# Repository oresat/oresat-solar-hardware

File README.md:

# OreSat Solar Modules

This repo contains the CAD for [OreSat's](oresat.org) solar modules. Part of OreSat's design is a module bus system that spans 1 - 3 U, so each array is its own 1U "panel". Oresat0, a 1U CubeSat, thus has 4 solar modules, and OreSat1, a 2U CubeSat, has 8. This approach has pretty severe drawbacks in terms of solar cell coverage area, but it's extremely flexible for having one design across a bunch of different designs. One nifty part of this design is that each 1u panel has its own **true** maximum power point tracker, with a software-defined MPPT algorithm. We're MPPT elitists - we eschew maximum power point "controllers" and think if it's not doing true power point optimization, you're just doing it wrong.

That and coffee. You're all doing coffee wrong, too, but we don't hold that against you, you don't live in Portland, we understand.

We've flown our GaAs solar cell design, and are currently workingon our silicon design.

# Design Notes

**Status, design, construction, and testing information can be found in the [OreSat Solar Module Design Notes](https://docs.google.com/document/d/1mogZjYhJievwLsnVkg4Q0sEF9xPMA5q7KPciky3YWKE/edit?usp=sharing).**

# Pretty Pictures

## LICENSE

Copyright the Portland State Aerospace Society, 2025.

This source describes Open Hardware that is licensed under CERN-OHL-S v2, or any later version.

You may redistribute and modify this source and make products using it under the terms of the CERN-OHL-S v2 (https://ohwr.org/cern_ohl_s_v2.txt).

This source is distributed WITHOUT ANY EXPRESS OR IMPLIED WARRANTY, INCLUDING OF MERCHANTABILITY, SATISFACTORY QUALITY AND FITNESS FOR A PARTICULAR PURPOSE. Please see the CERN-OHL-S v2 for applicable conditions.

Source location: https://github.com/oresat/

If you require a different license for this open hardware project, please contact us at [oresat@pdx.edu](mailto:oresat@pdx.edu).

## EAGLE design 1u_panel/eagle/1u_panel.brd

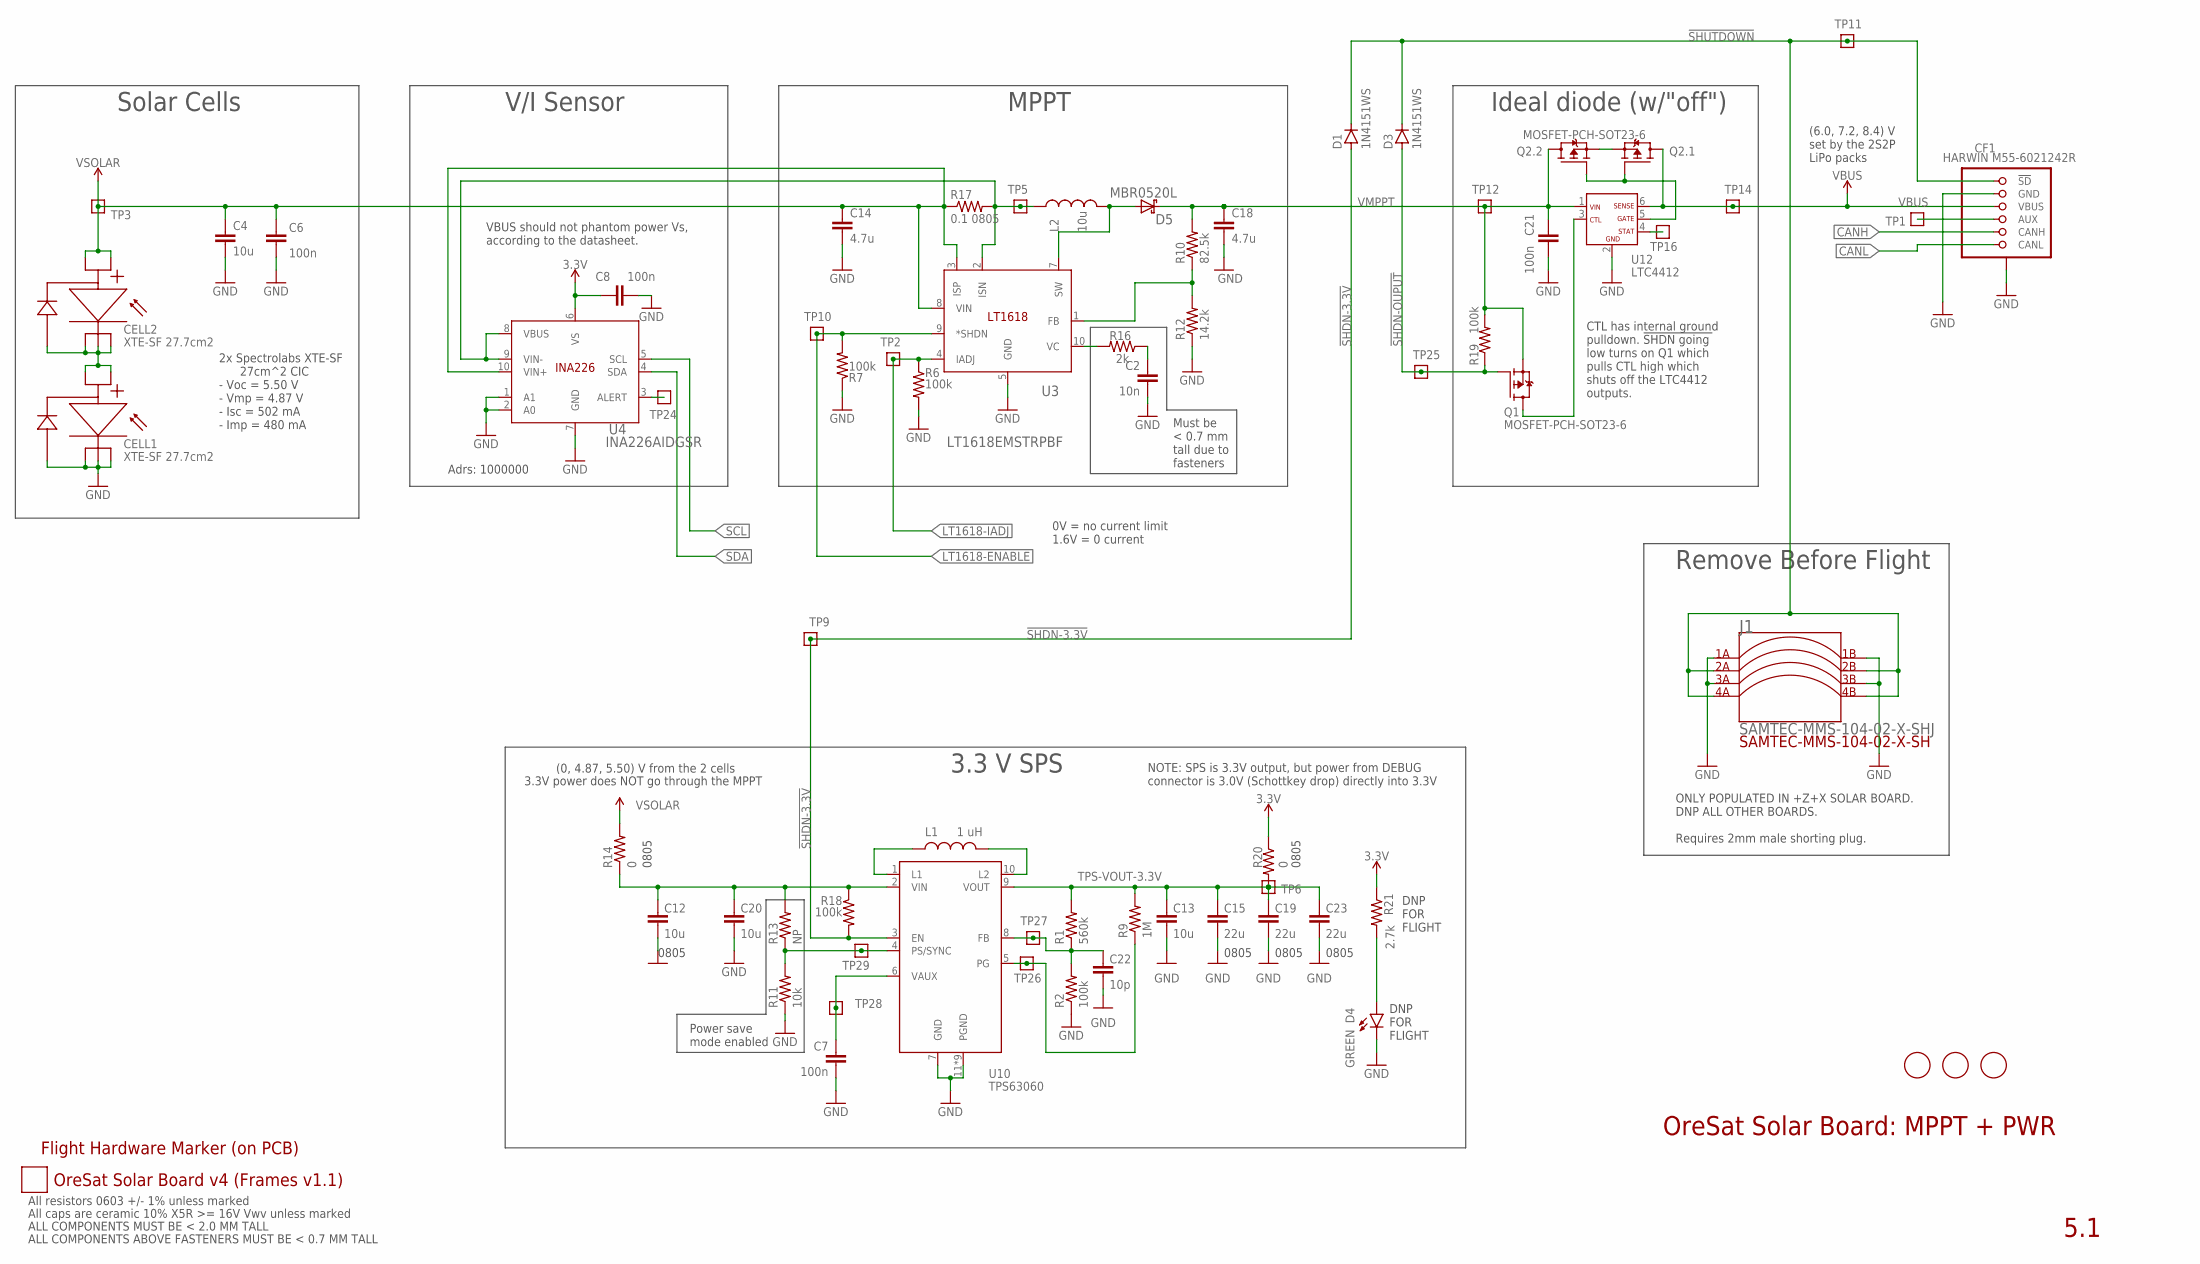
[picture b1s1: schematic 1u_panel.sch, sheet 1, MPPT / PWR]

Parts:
C2: 10n; .0603-C-NOSILK; MPN UMK107B7103KAHT
C4, C13, C20: 10u; .0603-C-NOSILK; MPN GRT188R61C106KE13D
C6, C7, C8: 100n; .0603-C-NOSILK; MPN CL10B104KB85PND
C12: 10u; .0805-B-NOSILK; MPN GRT21BR61C106KE01L
C14, C18: 4.7u; .0603-C-NOSILK; MPN EMK107BBJ475KAHT
C15, C19, C23: 22u; .0805-B-NOSILK; MPN CL32B226KOJVPNE
C21: 100n; .0402-B-NOSILK; MPN CL10B104KB85PND
C22: 10p; .0603-C-NOSILK; MPN GRT188R61C106KE13D
CELL1, CELL2: XTE-SF 27.7cm2; SPECTROLAB-XTE-SF
CF1: HARWIN M55-6021242R; HARWIN-M55-60X1242R
D1, D3: 1N4151WS; SOD323-R
D4: GREEN; LED-0603; MPN IN-S63AT5A
D5: MBR0520L; SOD123; MPN NRVB130T3G
J1: SAMTEC-MMS-104-02-X-SHJ; SAMTEC-MMS-104-02-X-SH
L1: 1 uH; IND_1226AS-H-1R0N=P2; MPN VLS3010CX-1R5M-1
L2: 10u; NONSTANDARD; MPN 744042100
PCB1: ORESAT-SOLAR-BOARD-V4-SPECTROLABS; ORESAT-SOLAR-BOARD-V4
Q1: MOSFET-PCH-SOT23-6; SOT23-6; MPN DMP3050LVT-7
Q2: MOSFET-PCH-SOT23-6; SOT23-6; MPN DMP2240UDM-7
R1: 560k; .0603-C-NOSILK; MPN CRGCQ0603F470K
R2: 100k; .0603-C-NOSILK; MPN RR0816P-104-D
R6, R7, R18, R19: 100k; .0603-C-NOSILK; MPN RNCP0603FTD10K0
R9: 1M; .0603-C-NOSILK
R10: 82.5k; .0603-C-NOSILK; MPN ERA-3AEB8252V
R11: 10k; .0603-C-NOSILK
R12: 14.2k; .0603-C-NOSILK; MPN RN73R1JTTD1422D25
R13: NP; .0603-C-NOSILK; MPN RNCP0603FTD10K0
R14, R20: 0; .0805-C-NOSILK; MPN RMCF0805ZT0R00
R16: 2k; .0603-C-NOSILK; MPN RK73H1JTTD2001F
R17: 0.1 0805; .0805-C-NOSILK; MPN RMCF0805ZT0R00
R21: 2.7k; .0603-C-NOSILK; MPN CRGCQ0603F2K7
TP1, TP2, TP3, TP5, TP6, TP9, TP10, TP11, TP12, TP14, TP16, TP24, TP25, TP26, TP27, TP28, TP29: TEST-POINT-LARGE-SQUARE; 1X01
U3: LT1618EMSTRPBF; MSOP-10_MS; MPN LT1618EMS#TRPBF
U4: INA226AIDGSR; DGS10; MPN INA226AIDGSR
U10: TPS63060; CONV_TPS63060DSCT
U12: LTC4412; SOT23-6; MPN LTC4412ES6#TRPBF
U$1: FLIGHMARKERNEW; FLIGHTMARKER_NEW_BOARDS
U$2, U$3, U$4: FIDUCIAL; FIDUCIAL_1MM

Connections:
3.3V: C8.1, R20.1, R21.1, U4.6 (VS); also elsewhere on the board
4412-CTL: Q1.1 (D), Q1.2 (D), Q1.5 (D), Q1.6 (D), U12.3 (CTL)
4412-GATE: Q2.1 (G), Q2.3 (G), U12.5 (GATE)
!SHDN-3.3V: D1.A, R18.2, TP9.1, U10.3 (EN)
!SHDN-OUPUT: D3.A, Q1.3 (G), R19.1, TP25.1
!SHUTDOWN: CF1.1 (!SD), CF1.2 (!SD), D1.C, D3.C, J1.2A, J1.2B, J1.4A, J1.4B, TP11.1
AUX: CF1.7 (AUX), CF1.8 (AUX), TP1.1
CANH: CF1.9 (CANH), CF1.10 (CANH); also elsewhere on the board
CANL: CF1.11 (CANL), CF1.12 (CANL); also elsewhere on the board
GND: C2.2, C4.2, C6.2, C7.2, C8.2, C12.2, C13.2, C14.2, C15.2, C18.2, C19.2, C20.2, C21.2, C22.2, C23.2, CELL1.NEG1 (C1), CELL1.NEG2 (C2), CELL1.NEG3 (C3), CELL1.NEG4 (C4), CF1.3 (GND), CF1.4 (GND), CF1.P$1 (SHIELD), CF1.P$2 (SHIELD), CF1.P$3 (SHIELD), CF1.P$4 (SHIELD), D4.C, J1.1A, J1.1B, J1.3A, J1.3B, R2.1, R6.2, R7.1, R11.1, R12.1, U3.5 (GND), U4.1 (A1), U4.2 (A0), U4.7 (GND), U10.7 (GND), U10.11 (PGND), U10.12 (PGND), U10.13 (PGND), U10.14 (PGND), U10.15 (PGND), U10.16 (PGND), U10.17 (PGND), U10.18 (PGND), U10.19 (PGND), U12.2 (GND); also elsewhere on the board
INTERCELL: CELL1.POS1 (A1), CELL1.POS2 (A2), CELL2.NEG1 (C1), CELL2.NEG2 (C2), CELL2.NEG3 (C3), CELL2.NEG4 (C4)
LT1618-ENABLE: R7.2, TP10.1, U3.9 (*SHDN); also elsewhere on the board
LT1618-FB: R10.1, R12.2, U3.1 (FB)
LT1618-IADJ: R6.1, TP2.1, U3.4 (IADJ); also elsewhere on the board
LT1618-ISN: L2.P$1 (1), R17.2, TP5.1, U3.2 (ISN), U4.8 (VBUS), U4.9 (VIN-)
LT1618-SW: D5.A (ANODE), L2.P$2 (2), U3.7 (SW)
LT1618-VC: R16.2, U3.10 (VC)
unnamed: TP24.1, U4.3 (ALERT)
unnamed: C2.1, R16.1
unnamed: TP16.1, U12.4 (STAT)
unnamed: Q2.2 (S), Q2.5 (S)
unnamed: D4.A, R21.2
SCL: U4.5 (SCL); also elsewhere on the board
SDA: U4.4 (SDA); also elsewhere on the board
TPS-EN: R11.2, R13.1, TP29.1, U10.4 (PS/SYNC)
TPS-FB: C22.1, R1.1, R2.2, TP27.1, U10.8 (FB)
TPS-L1: L1.1, U10.1 (L1)
TPS-L2: L1.2, U10.10 (L2)
TPS-PG: R9.1, TP26.1, U10.5 (PG)
TPS-VAUX: C7.1, TP28.1, U10.6 (VAUX)
TPS-VIN: C12.1, C20.1, R13.2, R14.1, R18.1, U10.2 (VIN)
TPS-VOUT-3.3V: C13.1, C15.1, C19.1, C23.1, R1.2, R9.2, R20.2, TP6.1, U10.9 (VOUT)
VBUS: CF1.5 (VBUS), CF1.6 (VBUS), Q2.6 (D), TP14.1, U12.6 (SENSE)
VMPPT: C18.1, C21.1, D5.K (CATHODE), Q1.4 (S), Q2.4 (D), R10.2, R19.2, TP12.1, U12.1 (VIN)
VSOLAR: C4.1, C6.1, C14.1, CELL2.POS1 (A1), CELL2.POS2 (A2), R14.2, R17.1, TP3.1, U3.3 (ISP), U3.8 (VIN), U4.10 (VIN+)

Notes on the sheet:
2x Spectrolabs XTE-SF 27cm^2 CIC - Voc = 5.50 V - Vmp = 4.87 V - Isc = 502 mA - Imp = 480 mA
OreSat Solar Board: MPPT + PWR
5.1
V/I Sensor
MPPT
All resistors 0603 +/- 1% unless marked
All caps are ceramic 10% X5R >= 16V Vwv unless marked
0805
(0, 4.87, 5.50) V from the 2 cells
(6.0, 7.2, 8.4) V set by the 2S2P LiPo packs
3.3 V SPS
VBUS should not phantom power Vs, according to the datasheet.
Adrs: 1000000
CTL has internal ground pulldown. !SHDN going low turns on Q1 which pulls CTL high which shuts off the LTC4412 outputs.
ALL COMPONENTS MUST BE < 2.0 MM TALL
ALL COMPONENTS ABOVE FASTENERS MUST BE < 0.7 MM TALL
3.3V power does NOT go through the MPPT
Must be < 0.7 mm tall due to fasteners
0V = no current limit 1.6V = 0 current
NOTE: SPS is 3.3V output, but power from DEBUG connector is 3.0V (Schottkey drop) directly into 3.3V
Solar Cells
Ideal diode (w/"off")
Remove Before Flight
ONLY POPULATED IN +Z+X SOLAR BOARD. DNP ALL OTHER BOARDS. Requires 2mm male shorting plug.
DNP FOR FLIGHT
Power save mode enabled

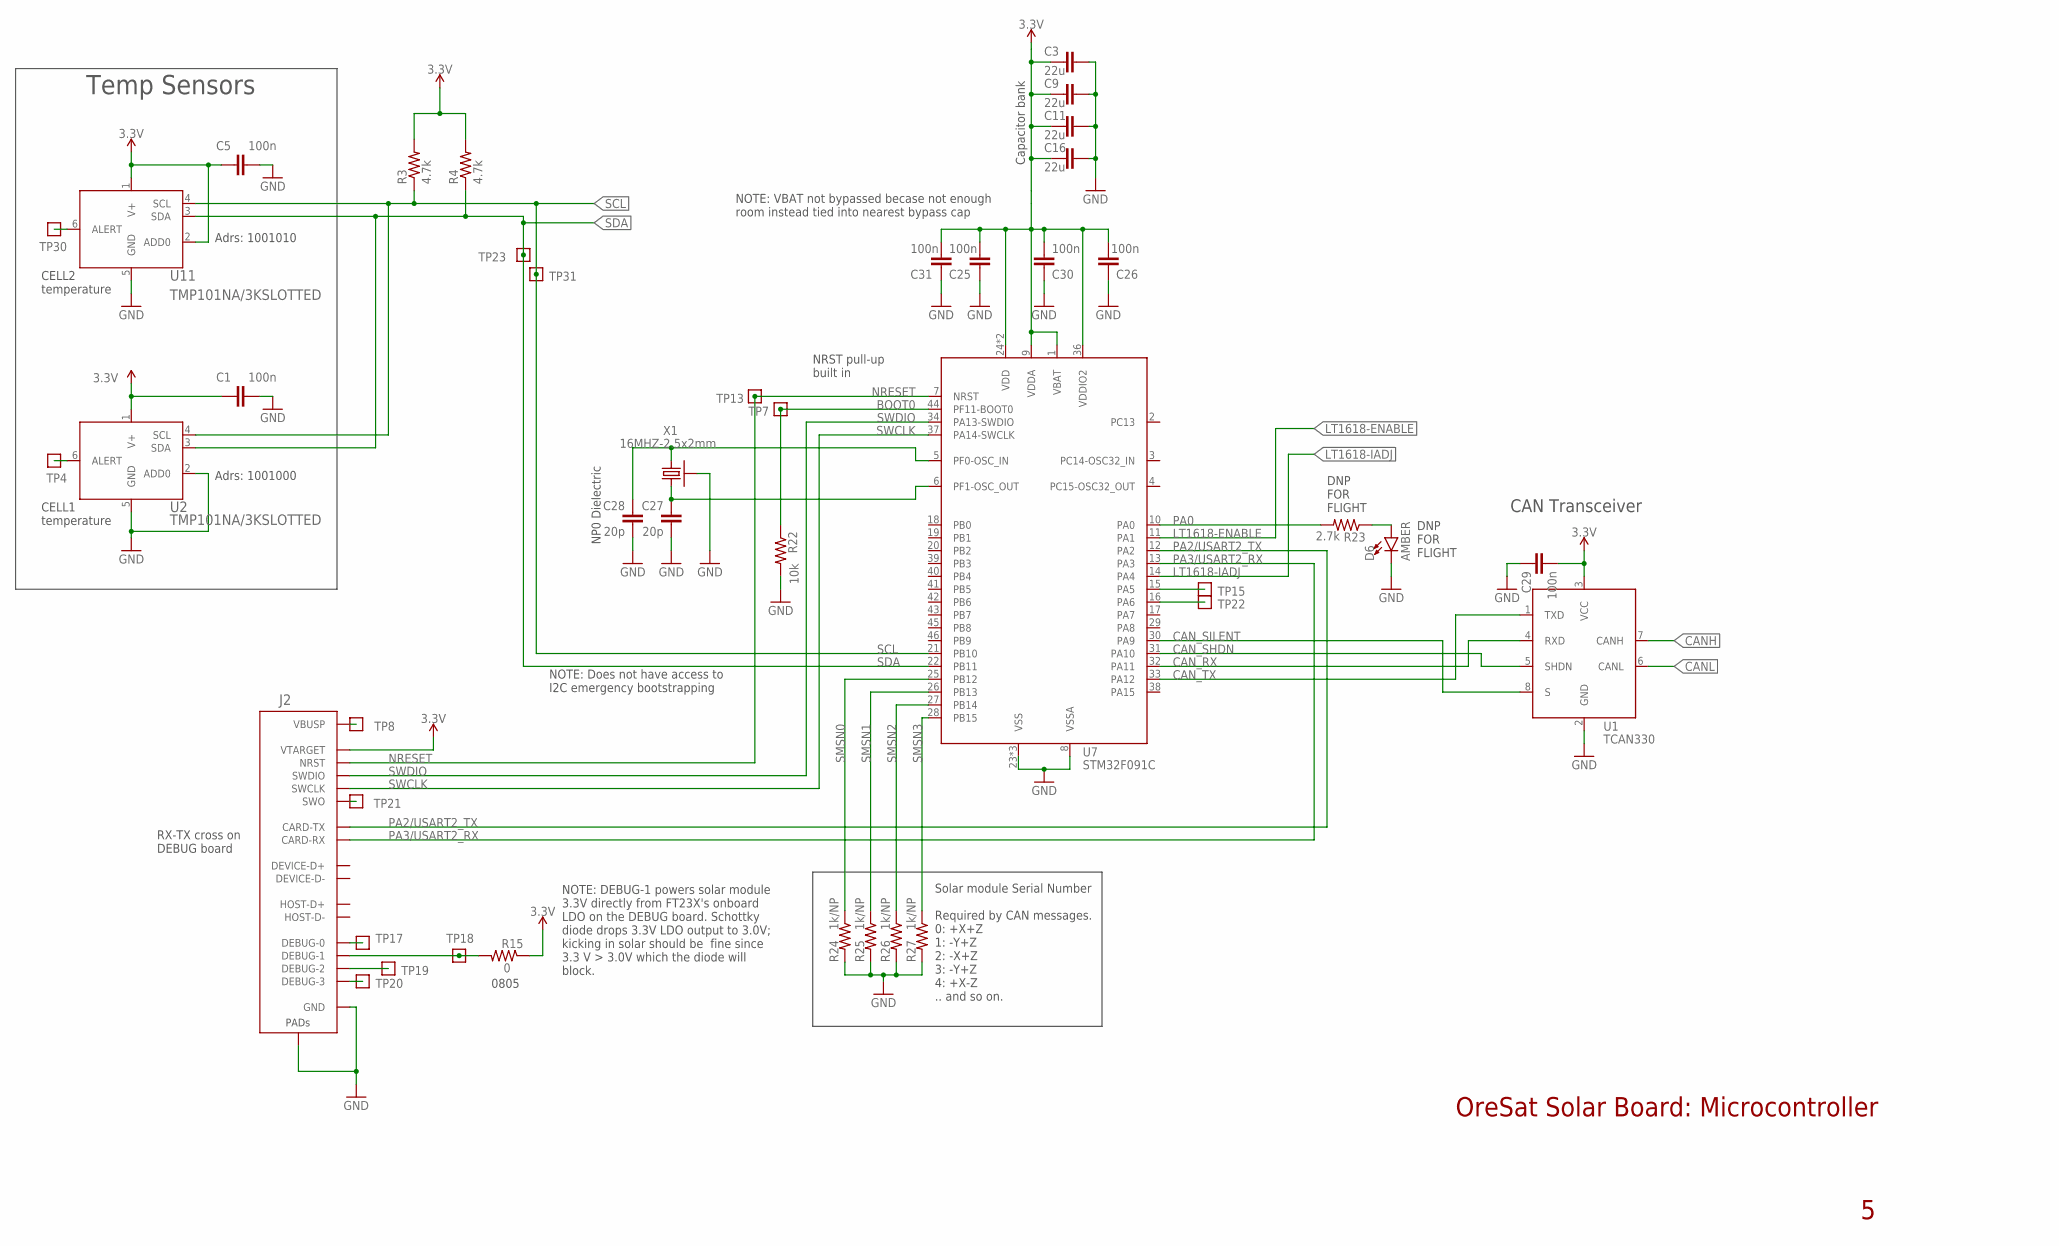
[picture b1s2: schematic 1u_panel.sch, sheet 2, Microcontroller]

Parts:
C1, C5, C25, C26, C29, C30, C31: 100n; .0603-C-NOSILK; MPN CL10B104KB85PND
C3, C9, C11, C16: 22u; .0805-B-NOSILK; MPN CL32B226KOJVPNE
C27, C28: 20p; .0603-C-NOSILK; MPN GCM1885C2A200JA16D
D6: AMBER; LED-0603; MPN IN-S63AT5A
J2: ORESAT-DEBUG-CONNECTOR-ALL; TE_2-1734592-0; MPN 687120183622
R3, R4: 4.7k; .0603-C-NOSILK; MPN RE0603FRE074K7L
R15: 0; .0805-C-NOSILK; MPN RMCF0805ZT0R00
R22: 10k; .0603-C-NOSILK; MPN CRGCQ0603F2K7
R23: 2.7k; .0603-C-NOSILK; MPN CRGCQ0603F2K7
R24, R25, R26, R27: 1k/NP; .0603-C-NOSILK; MPN CR0603AFX-1001ELF
TP4, TP7, TP8, TP13, TP15, TP17, TP18, TP19, TP20, TP21, TP22, TP23, TP30, TP31: TEST-POINT-LARGE-SQUARE; 1X01
U1: TCAN330; SOT23-8_TI-DCN; MPN TCAN330GDCNT
U2, U11: TMP101NA/3KSLOTTED; DBV6-SLOT; MPN TMP101NA/3K
U7: STM32F091C; MPN STM32F091CCT6TR
X1: 16MHZ-2.5x2mm; CRYSTAL_2.5X2; MPN ECS-160-10-36Q-ES-TR

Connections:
3.3V: C1.1, C3.1, C5.1, C9.1, C11.1, C16.1, C25.2, C26.2, C29.2, C30.2, C31.2, J2.11 (VTARGET), R3.2, R4.2, R15.1, U1.3 (VCC), U2.1 (V+), U7.1 (VBAT), U7.9 (VDDA), U7.24 (VDD), U7.36 (VDDIO2), U7.48 (VDD), U11.1 (V+), U11.2 (ADD0); also elsewhere on the board
BOOT0: R22.1, TP7.1, U7.44 (PF11-BOOT0)
CANH: U1.7 (CANH); also elsewhere on the board
CANL: U1.6 (CANL); also elsewhere on the board
CAN_RX: U1.4 (RXD), U7.32 (PA11)
CAN_SHDN: U1.5 (SHDN), U7.31 (PA10)
CAN_SILENT: U1.8 (S), U7.30 (PA9)
CAN_TX: U1.1 (TXD), U7.33 (PA12)
DEBU-1/SOLAR3V: J2.18 (DEBUG-1), R15.2, TP18.1
DEBUG-0: J2.17 (DEBUG-0), TP17.1
DEBUG-2: J2.19 (DEBUG-2), TP19.1
DEBUG-3: J2.20 (DEBUG-3), TP20.1
GND: C1.2, C3.2, C5.2, C9.2, C11.2, C16.2, C25.1, C26.1, C27.2, C28.2, C29.1, C30.1, C31.1, D6.C, J2.3 (GND), J2.6 (GND), J2.9 (GND), J2.PAD1 (PAD), J2.PAD2 (PAD), R22.2, R24.2, R25.2, R26.2, R27.2, U1.2 (GND), U2.2 (ADD0), U2.5 (GND), U7.8 (VSSA), U7.23 (VSS), U7.35 (VSS), U7.47 (VSS), U11.5 (GND), X1.2 (SHIELD), X1.4 (SHIELD); also elsewhere on the board
LT1618-ENABLE: U7.11 (PA1); also elsewhere on the board
LT1618-IADJ: U7.14 (PA4); also elsewhere on the board
unnamed: J2.1 (VBUSP), J2.2 (VBUSP), TP8.1
unnamed: TP4.1, U2.6 (ALERT)
unnamed: TP30.1, U11.6 (ALERT)
unnamed: D6.A, R23.1
NRESET: J2.10 (NRST), TP13.1, U7.7 (NRST)
PA0: R23.2, U7.10 (PA0)
PA2/USART2_TX: J2.13 (CARD-TX), U7.12 (PA2)
PA3/USART2_RX: J2.12 (CARD-RX), U7.13 (PA3)
PA5: TP15.1, U7.15 (PA5)
PA6: TP22.1, U7.16 (PA6)
SCL: R3.1, TP31.1, U2.4 (SCL), U7.21 (PB10), U11.4 (SCL); also elsewhere on the board
SDA: R4.1, TP23.1, U2.3 (SDA), U7.22 (PB11), U11.3 (SDA); also elsewhere on the board
SMSN0: R24.1, U7.25 (PB12)
SMSN1: R25.1, U7.26 (PB13)
SMSN2: R26.1, U7.27 (PB14)
SMSN3: R27.1, U7.28 (PB15)
SWCLK: J2.15 (SWCLK), U7.37 (PA14-SWCLK)
SWDIO: J2.14 (SWDIO), U7.34 (PA13-SWDIO)
SWO: J2.16 (SWO), TP21.1
XTAL1-IN: C28.1, U7.5 (PF0-OSC_IN), X1.1
XTAL1-OUT: C27.1, U7.6 (PF1-OSC_OUT), X1.3 (2)

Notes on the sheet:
Temp Sensors
Adrs: 1001010
NRST pull-up built in
CAN Transceiver
NOTE: VBAT not bypassed becase not enough room instead tied into nearest bypass cap
RX-TX cross on DEBUG board
NOTE: Does not have access to I2C emergency bootstrapping
Adrs: 1001000
NP0 Dielectric
0805
NOTE: DEBUG-1 powers solar module 3.3V directly from FT23X's onboard LDO on the DEBUG board. Schottky diode drops 3.3V LDO output to 3.0V; kicking in solar should be fine since 3.3 V > 3.0V which the diode will block.
CELL1 temperature
CELL2 temperature
DNP FOR FLIGHT
OreSat Solar Board: Microcontroller
Capacitor bank
Solar module Serial Number Required by CAN messages. 0: +X+Z 1: -Y+Z 2: -X+Z 3: -Y+Z 4: +X-Z .. and so on.

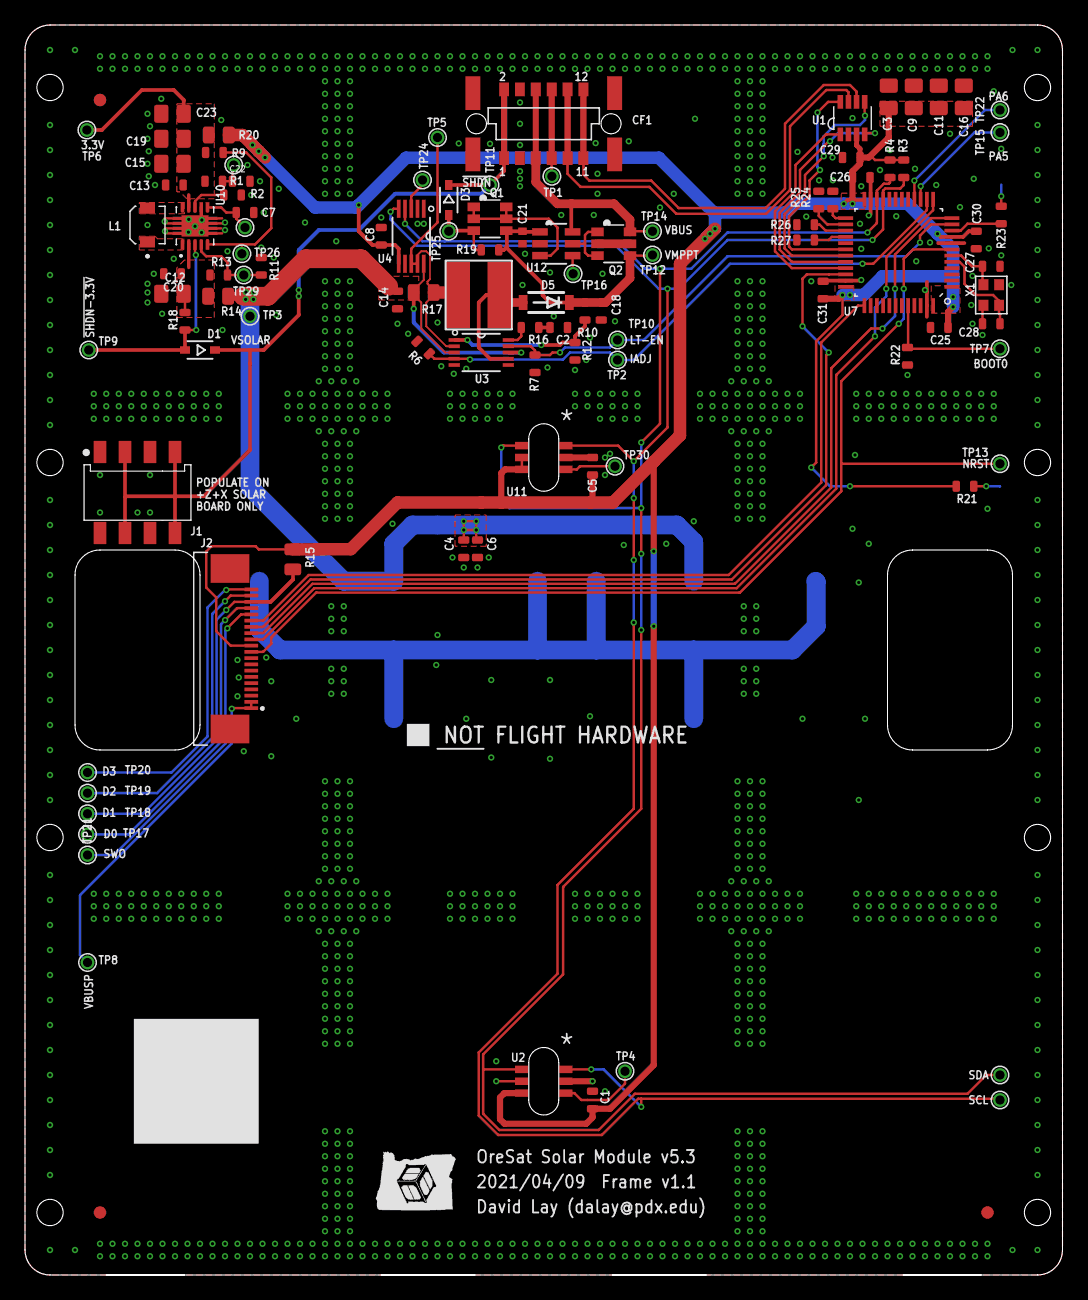
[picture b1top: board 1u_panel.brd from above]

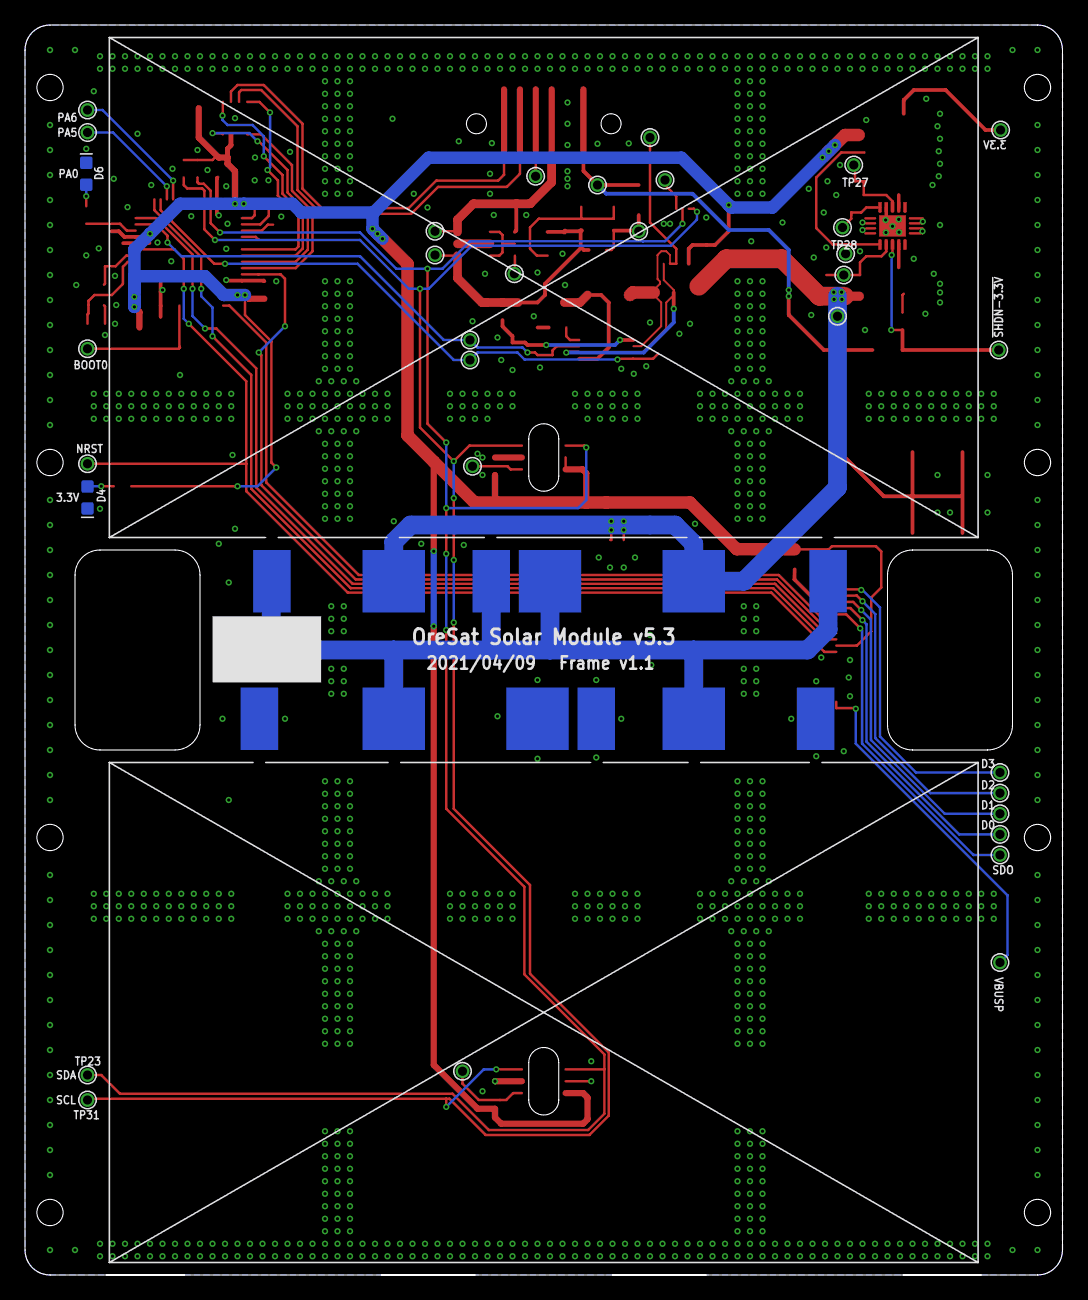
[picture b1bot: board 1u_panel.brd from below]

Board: 2 copper layers, 83.0 x 100.0 mm, 112 parts (4 on the bottom side), 63 nets.

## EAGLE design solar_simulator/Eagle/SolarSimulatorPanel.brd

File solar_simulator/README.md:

# Solar Simulator

# The Problem:  AKA Oh dear god why is everything so expensive

Because we wanted to test our solar panels in our thermal vacuum chamber, we needed a solar simulator that could simulate the AM0 light spectrum while also being compact, power efficient, and (most importantly) cheap!

Normal incandescent solutions were too bulky to fit in our tiny vacuum chamber, they require a lot of power, and dissipate a whole lot of heat into the system.  LED solutions do exist, but they are insanely expensive. So-being the loveable open source rogues that we are- decided to build our own!

# The Design
### LED SelectionThe wavelengths of light we care about ranges from about 376.5 nm - 899 nm (this is the approximate), meaning we can discard wavelengths in the AM0 spectrum outside of these bounds.  

We are only using three LED channels for our design (R, G, and B) most commercial simulators use way more channels than we do, but because our panels have a relatively flat response curve, and we don't care *that* much about super precision, we think we can get away with just 3.  So we split the wavelength spectrum into 3 roughly equal bands, and sum up the total irradiance found within the band.  This will give us the total irradiance needed for each band of LEDs.

Blue Irradiance(376.5 nm - 504.5 nm) = 221.9 W/m^2
Green Irradiance(505.5 nm - 637 nm) = 233.8 W/m^2
Red Irradiance(639 - 899 nm) = 161.5 W/m^2

Each channel is composed of CREE X-QE LEDs, because they are insanely small and power efficient and come in the wavelengths that work for us ( 440 nm, 520 nm, and 630 nm respectively).  In future revs we may shift our bands to better fit these wavelengths.  

### Driver Selection
Each channel is driven by a TPS92512 LED driver, since they can push stupid amounts of power at a very high frequency, and can be controlled with either a low frequency PWM from a microcontroller, or an analog input.  Each channel is in parallel and calculations are done assuming 56V Vin, meaning that the Vpp should be capable of 56V 3A. (NOTE: We could get away with lower voltages, but using 56V allows us to use a higher switching frequency of 1 MHz)

### Microcontroller
We are using an Arduino Nano (Atmega328P) as a daughter board to control the 3 LED LM3404HVs via an I2C DAC (MCP4728), as well as reading the 4 thermistors and reporting it over USB.  It is quick, dumb, and easy.  In the future we may move to an embedded microcontroller but this is easy enough for now.

 # Component Calculations

 Vin = 56 V

 Vout = 48.2 V (worst case)

 switching frequency = fsw = 1 MHz

* Output Inductor
  * NOTE: Iripple must be at least 75 mA for reliable operation.  400 mA chosen to decrease size of inductor.
  * L = (Vout * (Vin - Vout) ) / (Iripple * Vin * fsw)
      = (48.2 * (56-48.2) )/ (.4 * (56) * (10^6) )
      = 170 uH
* Maximum Duty Cycle
  * D = Vout/Vin
      = 56/48.2
      = 86%
* Input Capacitance
  * Note: ΔVin is assuming a 5% ripple on Vin
  * Cin = (Iled * D * (1-D) )/(ΔVin * fsw)
        = (1 * .86 * .14)/(2.8*10^6)
        = 43 nF
* Dynamic resistance of LEDs
  * Rled = (ΔVled/ΔIled) * #LED
         = .5 * 15
         = 7.5 Ω
* Output Capacitance
  * Zcout = (Rled * ΔI) / (Iripple - ΔI)
          = (7.5 * .05) / (.2 - .05)
          = 2.5 Ω
  * Cout = 1 / (2 * π * fsw * Zcout)
         = 1 / (2 * π * 10^6 * 2.5)
         = .15 uF
* Power Dissipation
  * Psw = D * Rds * Iled^2
        = .86 * .28 * 1^2
        = .24 W
  * Piq = Vin * (400 * 10^-6 + (.002 * fsw) / 10^6)
        = 56 * (400 * 10^-6 +  (.002*10^6) / 10^6)
        = .13 W
  * Pac = .73 * 10^-9 * fsw * Vin^2 * Iled
        = .73 * 10^-9 * 10^6 * 56^2 * 1
        = 2.29 W
  * Ptotal = (Psw + Piq + Pac) * #LEDDrivers
           = (.24 + .13 + 2.29) * 3
           = 2.66 * 3
           = 7.98 W

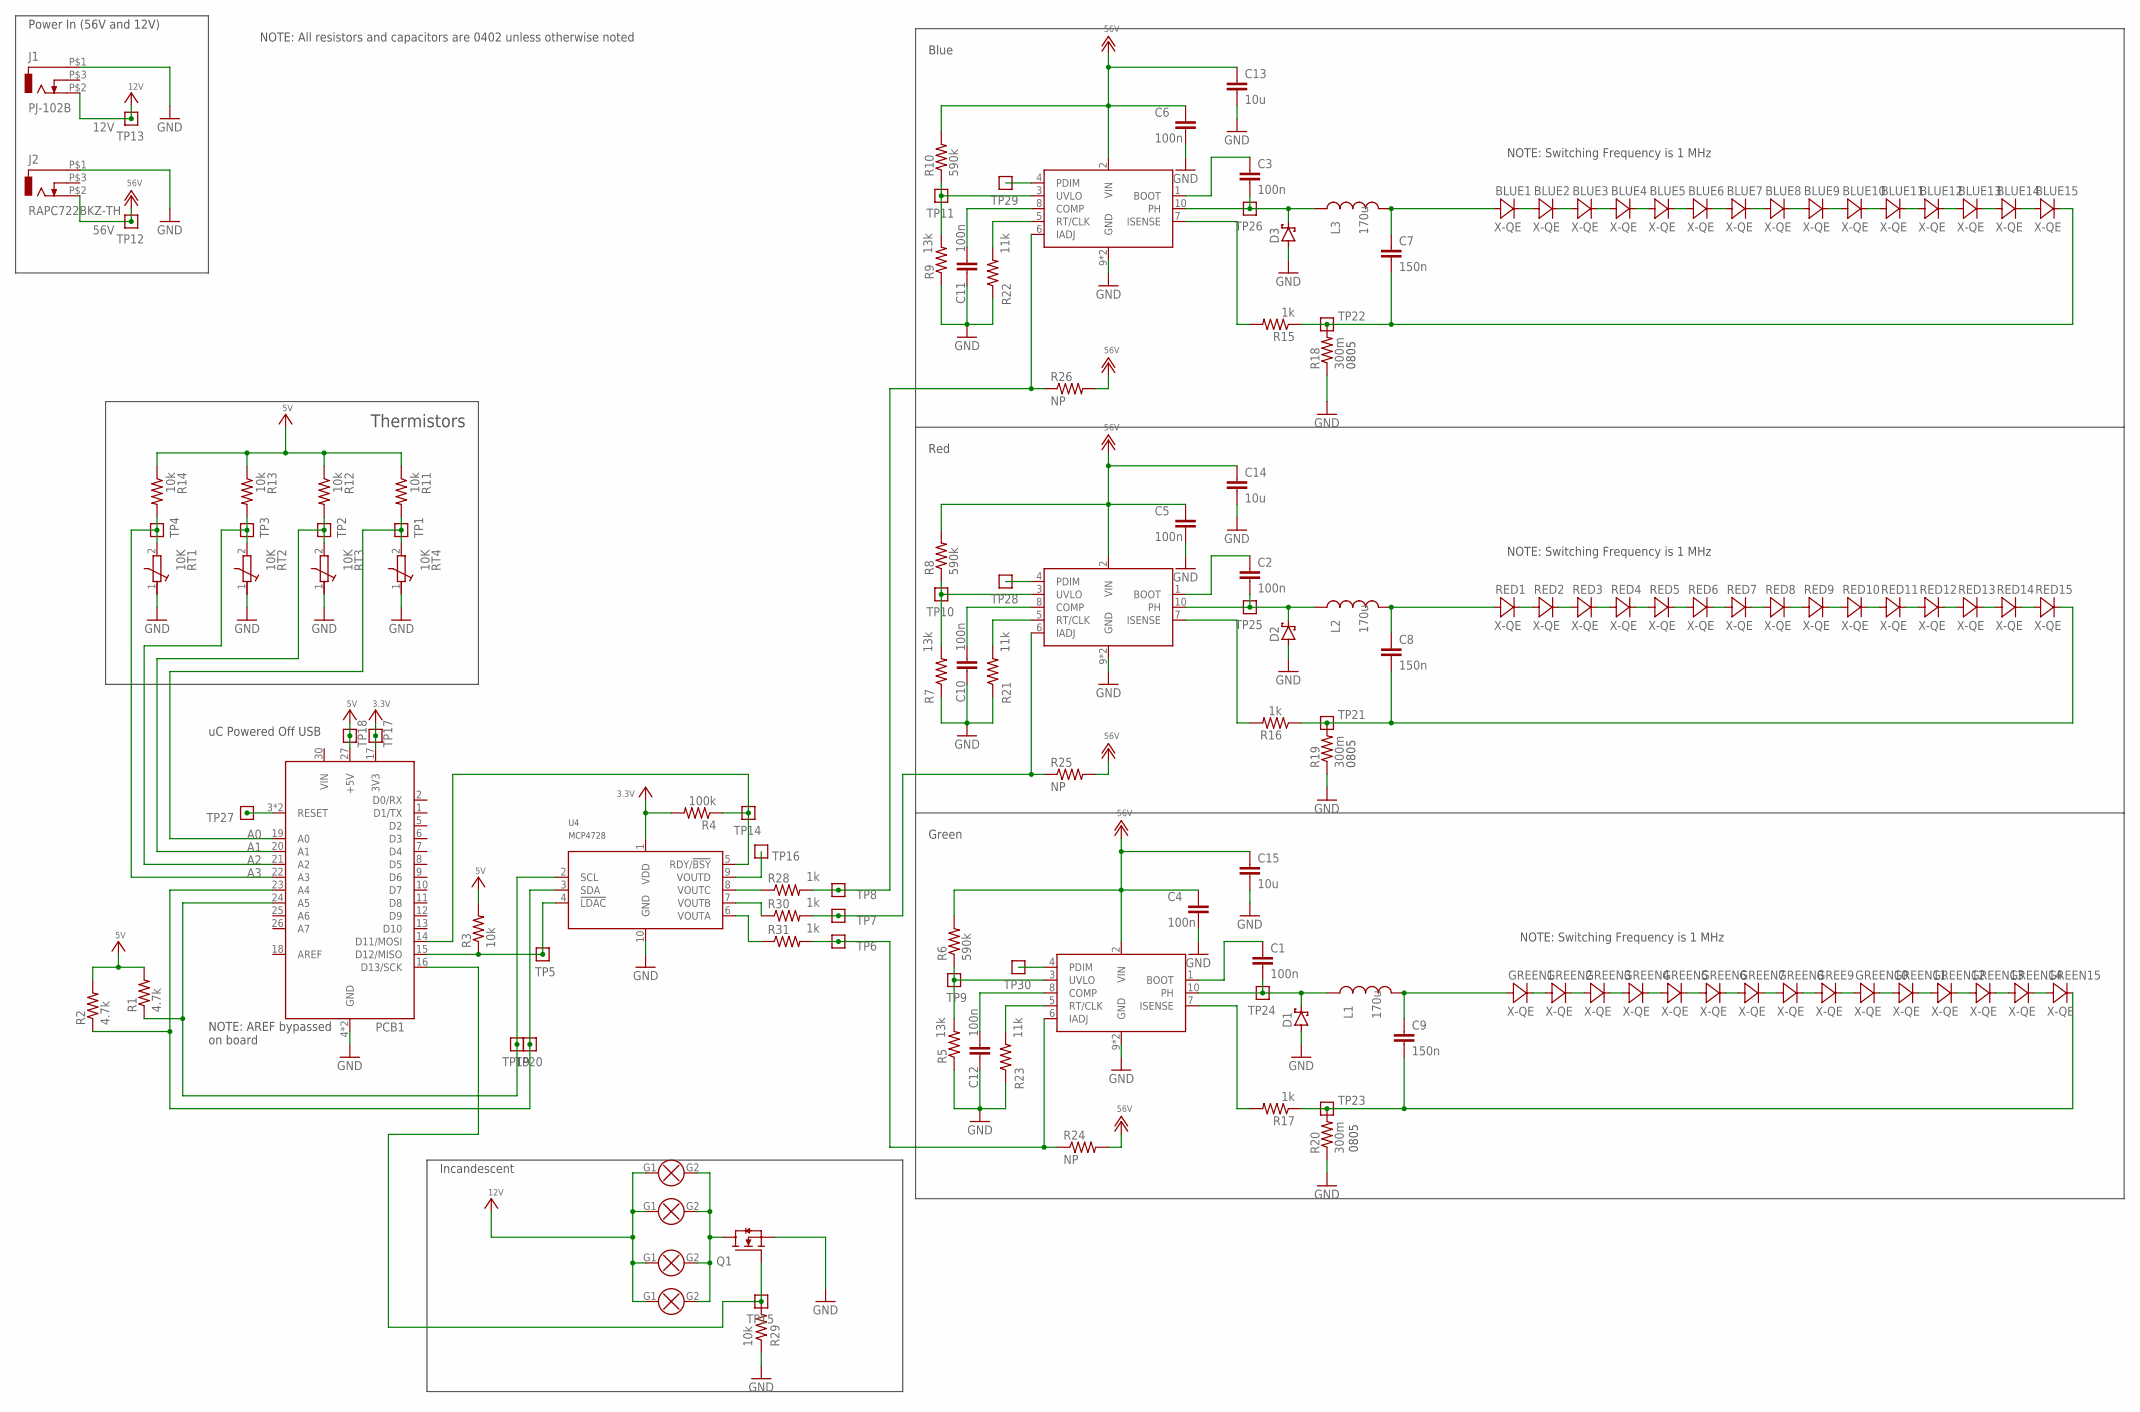
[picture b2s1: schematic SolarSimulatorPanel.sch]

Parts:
BLUE1, BLUE2, BLUE3, BLUE4, BLUE5, BLUE6, BLUE7, BLUE8, BLUE9, BLUE10, BLUE11, BLUE12, BLUE13, BLUE14, BLUE15: X-QE; MPN XQEROY-00-0000-000000L01
C1, C2, C4, C5, C6, C10, C11, C12: 100n; .0402-A-NOSILK; MPN GRM155R62A104KE14D
C3: 100n; .0402-A-NOSILK
C7, C8, C9: 150n; C0805K; MPN GRM188R71H154KAC4D
C13, C14, C15: 10u; C2220K; MPN 22201C106MAT2A
D1, D2, D3: D-MCC-SS2150; DO-214AC; MPN SS2150-LTP
GREE9: X-QE; MPN XQEGRN-00-0000-000000D03
GREEN1, GREEN2, GREEN3, GREEN4, GREEN5, GREEN6, GREEN7, GREEN8, GREEN10, GREEN11, GREEN12, GREEN13, GREEN14, GREEN15: X-QE; MPN XQEGRN-00-0000-000000D03
J1: PJ-102B; CUI_PJ-102B
J2: RAPC722BKZ-TH; RAPC722BKZ; MPN RAPC722BKZ
L1, L2, L3: 170u; 1212NONSTANDARD; MPN SH150S-1.02-168
PCB1: ARDUINO_NANO; ARDUINO_NANO_SHIELD
Q1: NCH-SOT223; SOT223; MPN DMN6068SE
R1: 4.7k; .0402-A-NOSILK; MPN RC0402JR-074K7L
R2: 4.7k; .0402-A-NOSILK; MPN 311-4.7KJRCT-ND
R3, R29: 10k; .0402-A-NOSILK; MPN RC0402FR-0710KL
R4: 100k; .0402-A-NOSILK
R5, R7, R9: 13k; .0402-A-NOSILK; MPN ERA-2AEB133X
R6, R8, R10: 590k; .0402-A-NOSILK; MPN RMCF0402FT590K
R11, R12, R13, R14: 10k; .0603-B-NOSILK; MPN RC0402FR-0710KL
R15, R16, R17: 1k; .0402-A-NOSILK; MPN RC0402FR-071KL
R18, R19, R20: 300m; R0805; MPN ERJ-6DQJR30V
R21, R22, R23: 11k; .0402-A-NOSILK; MPN ERA-3AEB113V
R24, R25, R26: NP; R0402
R28, R30, R31: 1k; R0402; MPN RC0402FR-071KL
RED1, RED2, RED3, RED4, RED5, RED6, RED7, RED8, RED9, RED10, RED11, RED12, RED13, RED14, RED15: X-QE; MPN XQERED-00-0000-000000701
RT1, RT2, RT3, RT4: 10K; R0402; MPN NTCG103JF103FT1
TP1, TP2, TP3, TP4, TP5, TP6, TP7, TP8, TP9, TP10, TP11, TP12, TP13, TP14, TP15, TP16, TP17, TP18, TP19, TP20, TP21, TP22, TP23, TP24, TP25, TP26, TP27, TP28, TP29, TP30: TEST-POINT; 2MM-TEST-POINT
U1, U2, U3: tps92512; MSOP10; MPN TPS92512DGQR
U4: MCP4728; MSOP10; MPN MCP4728T-E/UN
U$7, U$8, U$9, U$10: HL_G4BULB; G4BASE; MPN 3301

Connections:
3.3V: PCB1.17 (3V3), R4.2, TP17.1, U4.1 (VDD)
5V: PCB1.27 (+5V), R1.2, R2.2, R3.2, R11.1, R12.1, R13.1, R14.1, TP18.1
12V: J1.P$2 (3), TP13.1, U$7.G1, U$8.G1, U$9.G1, U$10.G1
56V: C4.1, C5.1, C6.1, C13.1, C14.1, C15.1, J2.P$2 (3), R6.2, R8.2, R10.2, R24.2, R25.2, R26.2, TP12.1, U1.2 (VIN), U2.2 (VIN), U3.2 (VIN)
88: RED5.CATHODE (C), RED6.ANODE (A)
!LDAC: PCB1.15 (D12/MISO), R3.1, TP5.1, U4.4 (!LDAC)
!RESET: PCB1.3 (RESET), PCB1.28 (RESET), TP27.1
A0: PCB1.19 (A0), R11.2, RT4.2 (E), TP1.1
A1: PCB1.20 (A1), R12.2, RT3.2 (E), TP2.1
A2: PCB1.21 (A2), R13.2, RT2.2 (E), TP3.1
A3: PCB1.22 (A3), R14.2, RT1.2 (E), TP4.1
AREF: PCB1.18 (AREF)
GND: C4.2, C5.2, C6.2, C10.2, C11.2, C12.2, C13.2, C14.2, C15.2, D1.A, D2.A, D3.A, J1.P$1 (1), J2.P$1 (1), PCB1.4 (GND), PCB1.29 (GND), Q1.3 (S), R5.1, R7.1, R9.1, R18.1, R19.1, R20.1, R21.1, R22.1, R23.1, R29.1, RT1.1 (A), RT2.1 (A), RT3.1 (A), RT4.1 (A), U1.9 (GND), U1.GND, U2.9 (GND), U2.GND, U3.9 (GND), U3.GND, U4.10 (GND)
unnamed: TP16.1, U4.9 (VOUTD)
unnamed: GREEN10.CATHODE (C), GREEN11.ANODE (A)
unnamed: R28.1, U4.8 (VOUTC)
unnamed: R30.1, U4.7 (VOUTB)
unnamed: RED6.CATHODE (C), RED7.ANODE (A)
unnamed: R5.2, R6.1, TP9.1, U3.3 (UVLO)
unnamed: RED7.CATHODE (C), RED8.ANODE (A)
unnamed: RED8.CATHODE (C), RED9.ANODE (A)
unnamed: BLUE9.CATHODE (C), BLUE10.ANODE (A)
unnamed: RED9.CATHODE (C), RED10.ANODE (A)
unnamed: RED11.CATHODE (C), RED12.ANODE (A)
unnamed: RED12.CATHODE (C), RED13.ANODE (A)
unnamed: RED13.CATHODE (C), RED14.ANODE (A)
unnamed: RED14.CATHODE (C), RED15.ANODE (A)
unnamed: RED1.CATHODE (C), RED2.ANODE (A)
unnamed: RED2.CATHODE (C), RED3.ANODE (A)
unnamed: RED3.CATHODE (C), RED4.ANODE (A)
unnamed: RED4.CATHODE (C), RED5.ANODE (A)
unnamed: R25.1, R30.2, TP7.1, U2.6 (IADJ)
unnamed: R23.2, U3.5 (RT/CLK)
unnamed: BLUE6.CATHODE (C), BLUE7.ANODE (A)
unnamed: BLUE7.CATHODE (C), BLUE8.ANODE (A)
unnamed: C3.2, D3.C, L3.P$1 (1), TP26.1, U1.10 (PH)
unnamed: BLUE8.CATHODE (C), BLUE9.ANODE (A)
unnamed: C2.2, D2.C, L2.P$1 (1), TP25.1, U2.10 (PH)
unnamed: C1.2, D1.C, L1.P$1 (1), TP24.1, U3.10 (PH)
unnamed: BLUE11.CATHODE (C), BLUE12.ANODE (A)
unnamed: BLUE12.CATHODE (C), BLUE13.ANODE (A)
unnamed: PCB1.14 (D11/MOSI), R4.1, TP14.1, U4.5 (RDY/!BSY)
unnamed: BLUE13.CATHODE (C), BLUE14.ANODE (A)
unnamed: BLUE14.CATHODE (C), BLUE15.ANODE (A)
unnamed: BLUE1.CATHODE (C), BLUE2.ANODE (A)
unnamed: R31.1, U4.6 (VOUTA)
unnamed: C12.1, U3.8 (COMP)
unnamed: C3.1, U1.1 (BOOT)
unnamed: GREEN1.CATHODE (C), GREEN2.ANODE (A)
unnamed: GREEN2.CATHODE (C), GREEN3.ANODE (A)
unnamed: GREEN3.CATHODE (C), GREEN4.ANODE (A)
unnamed: GREEN4.CATHODE (C), GREEN5.ANODE (A)
unnamed: GREEN6.CATHODE (C), GREEN7.ANODE (A)
unnamed: GREEN7.CATHODE (C), GREEN8.ANODE (A)
unnamed: GREE9.ANODE (A), GREEN8.CATHODE (C)
unnamed: GREE9.CATHODE (C), GREEN10.ANODE (A)
unnamed: GREEN11.CATHODE (C), GREEN12.ANODE (A)
unnamed: GREEN12.CATHODE (C), GREEN13.ANODE (A)
unnamed: GREEN13.CATHODE (C), GREEN14.ANODE (A)
unnamed: GREEN14.CATHODE (C), GREEN15.ANODE (A)
unnamed: C1.1, U3.1 (BOOT)
unnamed: BLUE2.CATHODE (C), BLUE3.ANODE (A)
unnamed: BLUE3.CATHODE (C), BLUE4.ANODE (A)
unnamed: BLUE4.CATHODE (C), BLUE5.ANODE (A)
unnamed: C2.1, U2.1 (BOOT)
unnamed: R7.2, R8.1, TP10.1, U2.3 (UVLO)
unnamed: R9.2, R10.1, TP11.1, U1.3 (UVLO)
unnamed: R16.2, U2.7 (ISENSE)
unnamed: R17.2, U3.7 (ISENSE)
unnamed: BLUE5.CATHODE (C), BLUE6.ANODE (A)
unnamed: BLUE10.CATHODE (C), BLUE11.ANODE (A)
unnamed: R15.2, U1.7 (ISENSE)
unnamed: C8.2, R16.1, R19.2, RED15.CATHODE (C), TP21.1
unnamed: C9.2, GREEN15.CATHODE (C), R17.1, R20.2, TP23.1
unnamed: R21.2, U2.5 (RT/CLK)
unnamed: R26.1, R28.2, TP8.1, U1.6 (IADJ)
unnamed: R22.2, U1.5 (RT/CLK)
unnamed: C10.1, U2.8 (COMP)
unnamed: C11.1, U1.8 (COMP)
unnamed: R24.1, R31.2, TP6.1, U3.6 (IADJ)
unnamed: C9.1, GREEN1.ANODE (A), L1.P$2 (2)
unnamed: C8.1, L2.P$2 (2), RED1.ANODE (A)
unnamed: BLUE15.CATHODE (C), C7.2, R15.1, R18.2, TP22.1
unnamed: BLUE1.ANODE (A), C7.1, L3.P$2 (2)
unnamed: Q1.2 (D), Q1.4 (D), U$7.G2, U$8.G2, U$9.G2, U$10.G2
unnamed: GREEN5.CATHODE (C), GREEN6.ANODE (A)
unnamed: PCB1.16 (D13/SCK), Q1.1 (G), R29.2, TP15.1
unnamed: TP30.1, U3.4 (PDIM)
unnamed: TP28.1, U2.4 (PDIM)
unnamed: TP29.1, U1.4 (PDIM)
unnamed: RED10.CATHODE (C), RED11.ANODE (A)
SCL: PCB1.24 (A5), R1.1, TP19.1, U4.2 (SCL)
SDA: PCB1.23 (A4), R2.1, TP20.1, U4.3 (SDA)
VIN: PCB1.30 (VIN)

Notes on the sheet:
Thermistors
Power In (56V and 12V)
Incandescent
Green
Red
Blue
NOTE: AREF bypassed on board
NOTE: Switching Frequency is 1 MHz
0805
NOTE: All resistors and capacitors are 0402 unless otherwise noted
uC Powered Off USB

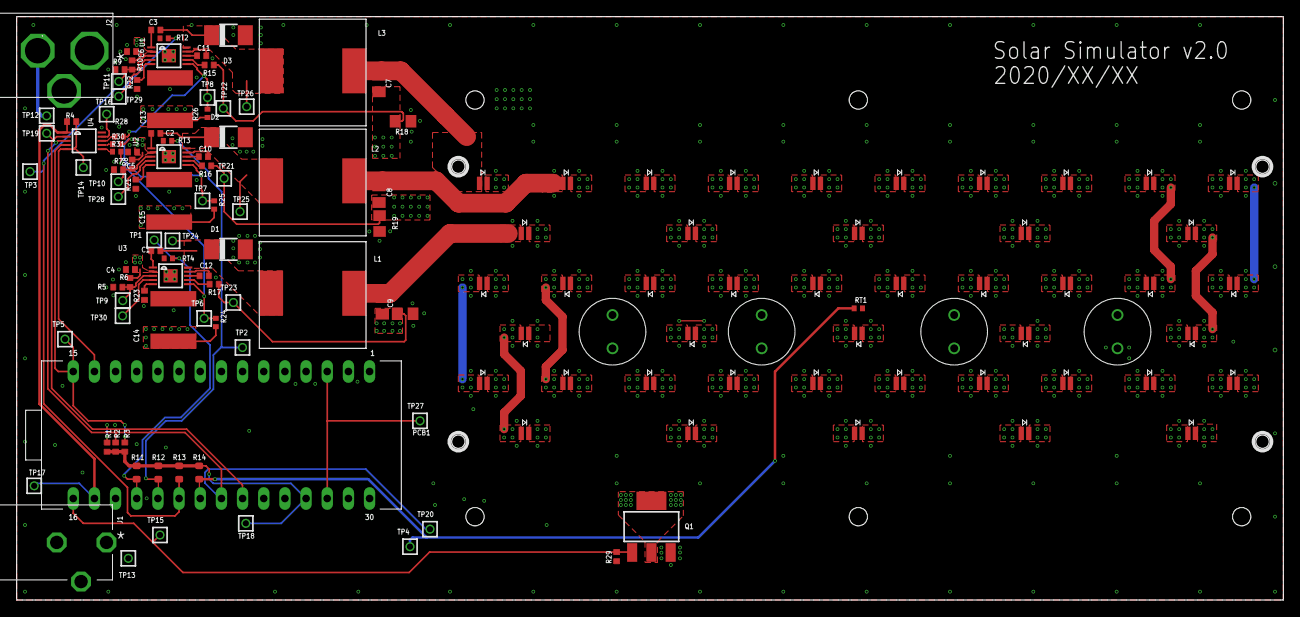
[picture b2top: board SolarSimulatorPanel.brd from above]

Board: 4 copper layers, 152.0 x 70.0 mm, 142 parts (0 on the bottom side), 92 nets.

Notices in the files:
parts and their libraries:
SparkFun-LED: Licensing: Creative Commons ShareAlike 4.0 International - https://creativecommons.org/licenses/by-sa/4.0
